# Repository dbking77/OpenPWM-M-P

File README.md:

OpenPWM-M-P
===========

A single channel motor driver for dc brushed motors utiliizing a attiny and a ZXBM5210 motor driver

At this time, this project is distributed under the TAPR Open Hardware License: http://www.tapr.org/ohl.html

These drivers use a resistor to control the max trip current. 

We assume that the desired trip current is right at the max for the driver, ow, 2 amps. 

Using the examples supplied in the data sheet, we would need a 0.25 ohm Rs resistor. Though, that resistor would need to be a 1 watt resistor. 

We would like to make the resistor smaller than a 1 watt surface mount resistor. So, we made the pad a 0805 pad. The max dissipation you can get out of a 0805 resistor is 1/3 watt. 

By altering VRef, we can alter the power disapated by the resistor. 

The resistor will see connect upto VRfef and ground.

If we select a lower cost resistor of 0.047 ohms ( http://www.digikey.com/scripts/DkSearch/dksus.dll?Detail&itemSeq=165686396 )

The equation for what the trip current(assuming that the trip current is 2) is:

ItripMax(2) = Vref / (Rs * 10)
2 = Vref / 0.47
Vref = 0.94V

The resistor should only see 0.04 watts if Vref is kept to 0.94.

Project owned by Michael Gregg(mgregg@-at-@michaelgregg.com) and Derr(dbking77@-at@gmail.com)

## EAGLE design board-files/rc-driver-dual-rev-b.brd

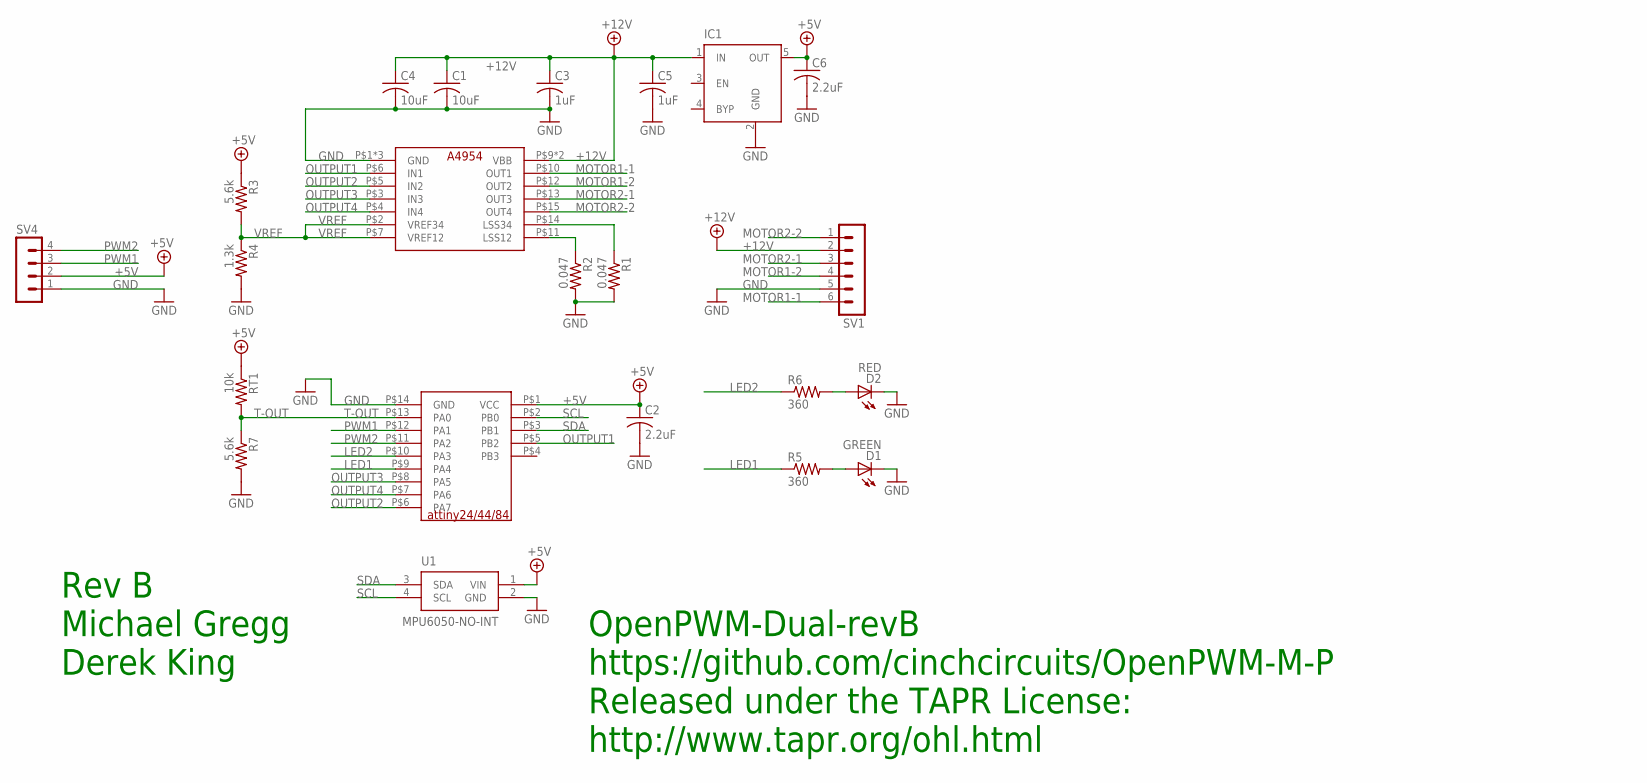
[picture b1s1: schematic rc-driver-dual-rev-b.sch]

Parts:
C1, C4: 10uF; C1206
C2, C6: 2.2uF; C0603
C3, C5: 1uF; C0603
D1: GREEN; CHIPLED_0603
D2: RED; CHIPLED_0603
IC1: MIC5219XX; SOT23-5; MPN TPS70950
R1, R2: 0.047; R0805
R3, R7: 5.6k; R0402
R4: 1.3k; R0402
R5, R6: 360; R0402
RT1: 10k; R0402
SV1: MA06-1
SV4: MA04-1
U1: MPU6050-NO-INT
U$1: ATTINY24A; SOIC-14-WIDE
U$2: A4954-DUAL-HBRIDGE; TSSOP-16-LP

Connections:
+5V: C2.1, C6.1, IC1.5 (OUT), R3.1, RT1.1, SV4.2, U1.1 (VIN), U$1.P$1 (VCC)
+12V: C1.1, C3.1, C4.1, C5.1, IC1.1 (IN), SV1.2, U$2.P$9 (VBB), U$2.P$16 (VBB)
GND: C1.2, C2.2, C3.2, C4.2, C5.2, C6.2, D1.C, D2.C, IC1.2 (GND), R1.2, R2.2, R4.2, R7.2, SV1.5, SV4.1, U1.2 (GND), U$1.P$14 (GND), U$2.P$1 (GND), U$2.P$8 (GND), U$2.P$17 (GND)
LED1: R5.1, U$1.P$9 (PA4)
LED2: R6.1, U$1.P$10 (PA3)
MOTOR1-1: SV1.6, U$2.P$10 (OUT1)
MOTOR1-2: SV1.4, U$2.P$12 (OUT2)
MOTOR2-1: SV1.3, U$2.P$13 (OUT3)
MOTOR2-2: SV1.1, U$2.P$15 (OUT4)
unnamed: R1.1, U$2.P$14 (LSS34)
unnamed: R2.1, U$2.P$11 (LSS12)
unnamed: D2.A, R6.2
unnamed: D1.A, R5.2
OUTPUT1: U$1.P$5 (PB2), U$2.P$6 (IN1)
OUTPUT2: U$1.P$6 (PA7), U$2.P$5 (IN2)
OUTPUT3: U$1.P$8 (PA5), U$2.P$3 (IN3)
OUTPUT4: U$1.P$7 (PA6), U$2.P$4 (IN4)
PWM1: SV4.3, U$1.P$12 (PA1)
PWM2: SV4.4, U$1.P$11 (PA2)
SCL: U1.4 (SCL), U$1.P$2 (PB0)
SDA: U1.3 (SDA), U$1.P$3 (PB1)
T-OUT: R7.1, RT1.2, U$1.P$13 (PA0)
VREF: R3.2, R4.1, U$2.P$2 (VREF34), U$2.P$7 (VREF12)

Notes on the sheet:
OpenPWM-Dual-revB
https://github.com/cinchcircuits/OpenPWM-M-P
Released under the TAPR License:
http://www.tapr.org/ohl.html
Rev B
Michael Gregg
Derek King

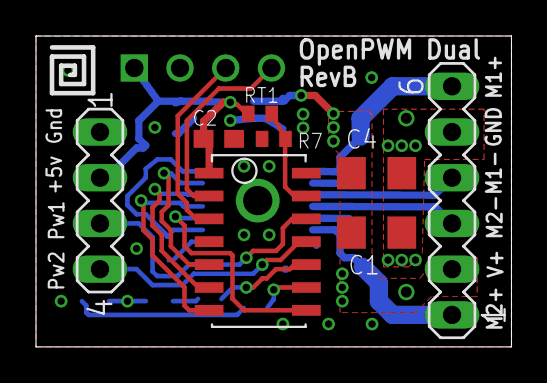
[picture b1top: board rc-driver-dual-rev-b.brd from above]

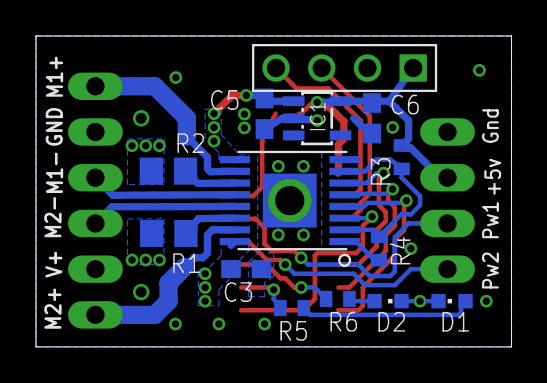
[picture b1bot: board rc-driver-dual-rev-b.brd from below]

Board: 2 copper layers, 26.4 x 17.3 mm, 22 parts (14 on the bottom side), 23 nets.

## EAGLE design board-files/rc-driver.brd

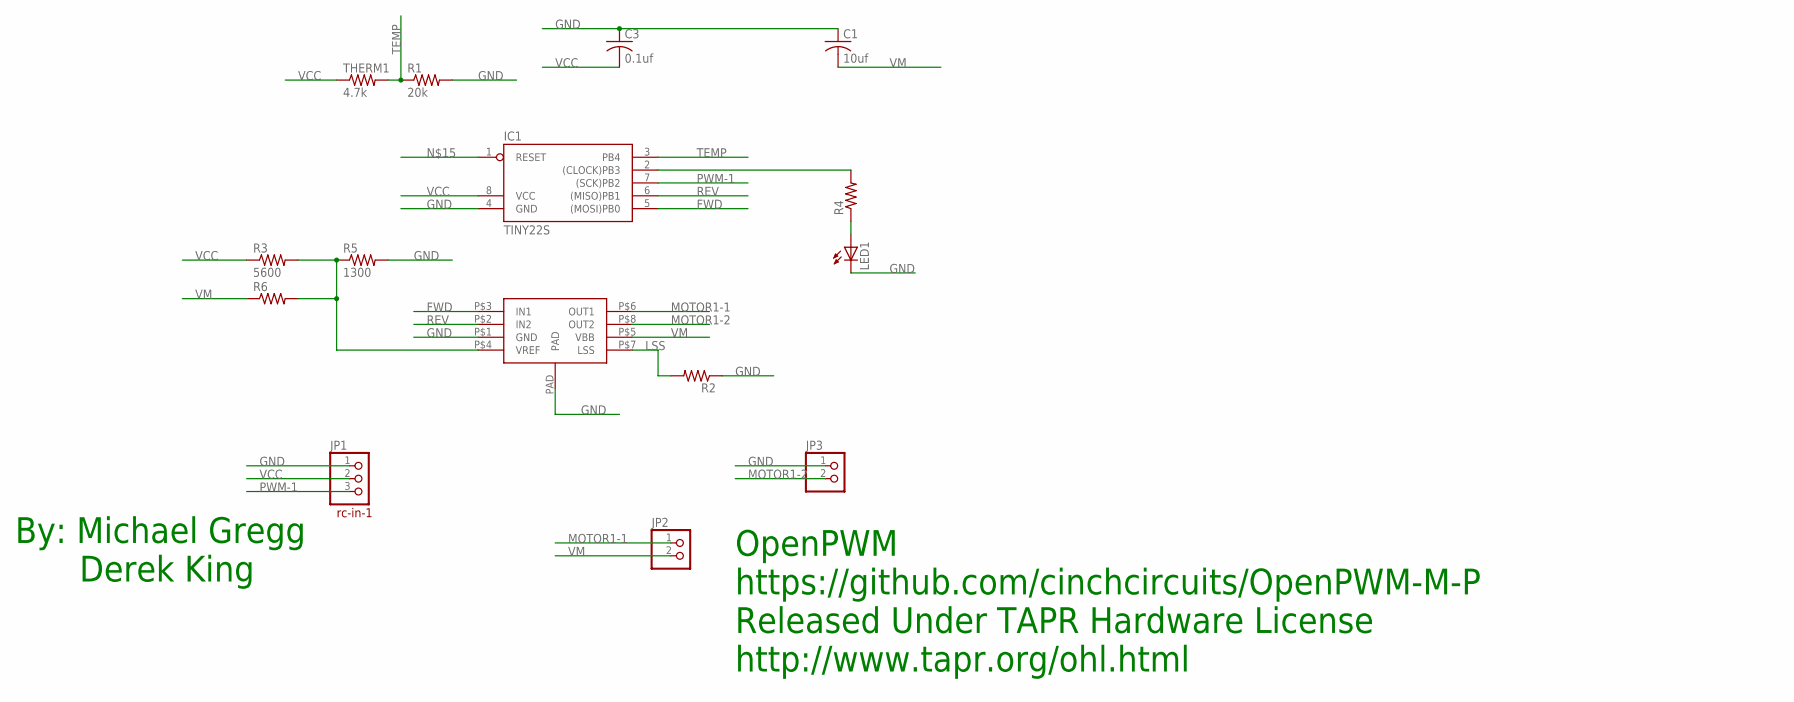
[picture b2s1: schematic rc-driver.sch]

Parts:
C1: 10uf; C1210
C3: 0.1uf; C0805
IC1: TINY22S; SOIC8
JP1: PINHD-1X3; 1X03
JP2, JP3: PINHD-1X2; 1X02
LED1: LEDCHIP-LED0603; CHIP-LED0603
R1: 20k; R0603
R2: R-US_R0805W; R0805W
R3: 5600; R0603
R4, R6: R-US_R0603; R0603
R5: 1300; R0603
THERM1: 4.7k; R0603
U$1: A4950-HBRIDGE; SO-8EP

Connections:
FWD: IC1.5 ((MOSI)PB0), U$1.P$3 (IN1)
GND: C1.1, C3.1, IC1.4 (GND), JP1.1, JP3.1, LED1.C, R1.2, R2.1, R5.2, U$1.P$1 (GND), U$1.PAD
LSS: R2.2, U$1.P$7 (LSS)
MOTOR1-1: JP2.1, U$1.P$6 (OUT1)
MOTOR1-2: JP3.2, U$1.P$8 (OUT2)
unnamed: R3.2, R5.1, R6.2, U$1.P$4 (VREF)
unnamed: IC1.2 ((CLOCK)PB3), R4.2
unnamed: LED1.A, R4.1
PWM-1: IC1.7 ((SCK)PB2), JP1.3
REV: IC1.6 ((MISO)PB1), U$1.P$2 (IN2)
TEMP: IC1.3 (PB4), R1.1, THERM1.2
VCC: C3.2, IC1.8 (VCC), JP1.2, R3.1, THERM1.1
VM: C1.2, JP2.2, R6.1, U$1.P$5 (VBB)

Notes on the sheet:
rc-in-1
By: Michael Gregg
Derek King
OpenPWM
https://github.com/cinchcircuits/OpenPWM-M-P
Released Under TAPR Hardware License
http://www.tapr.org/ohl.html

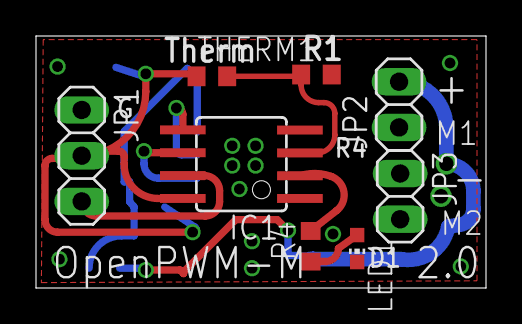
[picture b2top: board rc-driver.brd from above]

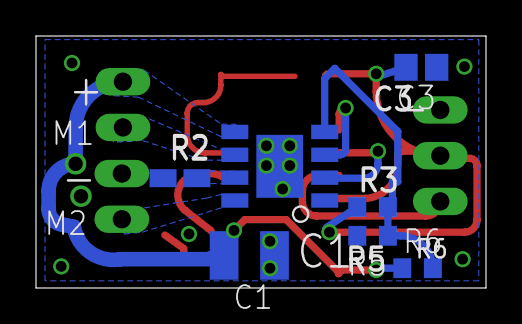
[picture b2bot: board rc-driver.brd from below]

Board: 2 copper layers, 25.0 x 14.0 mm, 15 parts (7 on the bottom side), 13 nets.

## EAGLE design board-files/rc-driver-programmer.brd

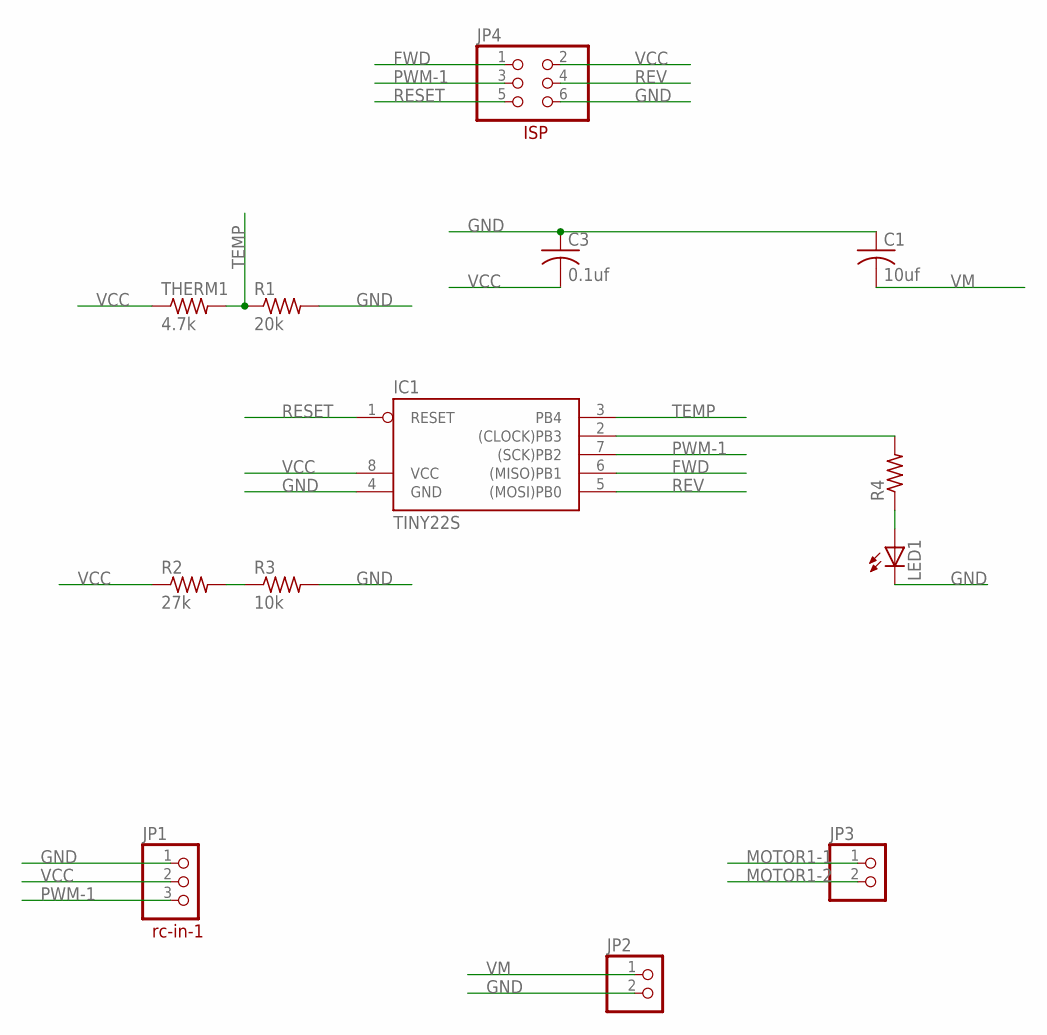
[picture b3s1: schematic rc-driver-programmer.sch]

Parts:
C1: 10uf; C1210
C3: 0.1uf; C0805
IC1: TINY22S; SOIC8
JP1: PINHD-1X3; 1X03
JP2, JP3: PINHD-1X2; 1X02
JP4: PINHD-2X3; 2X03
LED1: LEDCHIP-LED0603; CHIP-LED0603
R1: 20k; R0603
R2: 27k; R0603
R3: 10k; R0603
R4: R-US_R0603; R0603
THERM1: 4.7k; R0603

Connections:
FWD: IC1.6 ((MISO)PB1), JP4.1
GND: C1.1, C3.1, IC1.4 (GND), JP1.1, JP2.2, JP4.6, LED1.C, R1.2, R3.2
MOTOR1-1: JP3.1
MOTOR1-2: JP3.2
unnamed: IC1.2 ((CLOCK)PB3), R4.2
unnamed: LED1.A, R4.1
unnamed: R2.2, R3.1
PWM-1: IC1.7 ((SCK)PB2), JP1.3, JP4.3
RESET: IC1.1 (RESET), JP4.5
REV: IC1.5 ((MOSI)PB0), JP4.4
TEMP: IC1.3 (PB4), R1.1, THERM1.2
VCC: C3.2, IC1.8 (VCC), JP1.2, JP4.2, R2.1, THERM1.1
VM: C1.2, JP2.1

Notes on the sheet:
rc-in-1
ISP

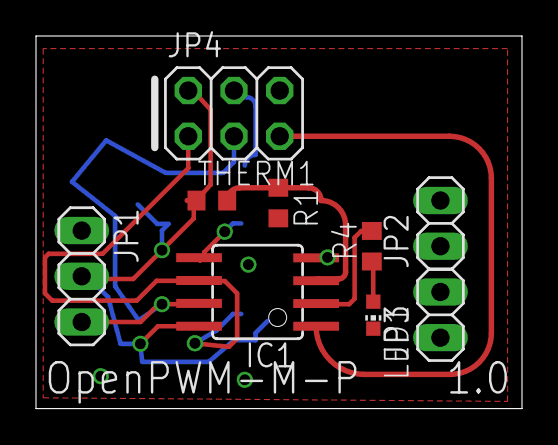
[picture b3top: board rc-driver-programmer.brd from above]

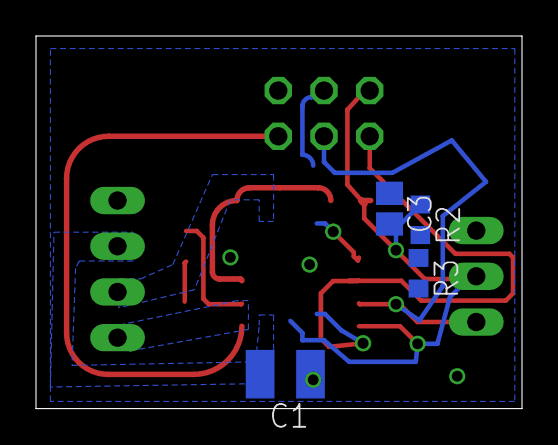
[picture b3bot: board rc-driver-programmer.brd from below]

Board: 2 copper layers, 27.0 x 20.7 mm, 13 parts (4 on the bottom side), 11 nets.

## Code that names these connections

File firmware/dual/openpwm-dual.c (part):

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#define PWM2_PIN 2

// Used to indicate error has occurred
#define LED2_PORT PORTA
#define LED2_DDR DDRA
#define LED2_PIN 3

// Used to indicate that input signal is being recv'ed
#define LED1_PORT PORTA
#define LED1_DDR DDRA
#define LED1_PIN 4


void gpioInit()
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    (0<<TOUT_PIN) |
    (0<<PWM1_PIN) |
    (0<<PWM2_PIN) |
    (1<<LED2_PIN) | 
    (1<<LED1_PIN) |
    (1<<OUT3_PIN) |
    (1<<OUT4_PIN) |
    (1<<OUT2_PIN) ;
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  PORTA =
    (1<<PWM1_PIN) |
    (1<<PWM2_PIN) |
    (1<<LED2_PIN) |
    (1<<LED1_PIN) ;
  
  DDRB = 
    (1<<OUT1_PIN);
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 *  output1 and output2 are a pair
 *  output2 and output4 are a pair
 *  
 *  output1 : PB2 : OC0A
 *  output2 : PA7 : OC0B
 *  output3 : PA5 : OC1B
 *  output4 : PA6 : OC1A
 */


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 *    value of -255 = full reverse
 *    value of 0 = stop/brake
 * 
 * out1 = PB2 = OC0A
 * out2 = PA7 = OC0B
 */
void setMotor1(int16_t duty)
{
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 *    value of -255 = full reverse
 *    value of 0 = stop/brake
 * 
 * out3 = PA5 = OC1B
 * out4 = PA6 = OC1A
 */
void setMotor2(int16_t duty)
{
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  {
    ++cnt.hi;
    // debug toggle LED everytime this occurs
    //LED2_PORT ^= (1<<LED2_PIN);
  }
  return cnt.val;
}
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    else
    {
      // debug toggle LED when bad pulse width is seen
      // LED1_PORT ^= (1<<LED1_PIN);
    }
  }
}
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 * generate a 16bit timestamp value that alows a servo pulse between
 * 1 and 2ms to be measured.
 * 
 * PA1 : PWM1 : PCINT1
 * PA2 : PWM2 : PCINT2
 */
uint8_t pcint_last_in;
ISR(PCINT0_vect)
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  // measure servo pwm pulse
  TIMSK0 = (1<<TOIE0);  

  // Enabled PCINT1 and PCINT2 for PA1 and PA2 pin change interrupts
  PCMSK0 = (1<<PCINT1) | (1<<PCINT2);
  GIMSK = (1<<PCIE0);
  pcint_last_in = PINA;
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      if (ovf_counter > 62)
      {
        ovf_counter = 0;
        //LED1_PORT ^= (1<<LED1_PIN);
        // when overflow counter reaches 62 it means about 
        // 62*256/8Mhz = 1.984ms have elapsed
        uint16_t time = getTimestamp();
        if (timeoutServoPwm(&pwm1, time) || timeoutServoPwm(&pwm2, time))
        {
          // servo signals stopped comming in, disable motors
          LED1_PORT &= ~(1<<LED1_PIN);
          LED2_PORT |= (1<<LED2_PIN);
          disableMotors();
          stable_counter = 0;
        }
        else 
        {
          LED1_PORT |= (1<<LED1_PIN);
          LED2_PORT &= ~(1<<LED2_PIN);

          // calculate new duty values from servo values
          // assume:
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
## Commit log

2014-12-25 Updating README.md to include license and ownership info.
2014-12-25 Adding first version of the board files. Including the gerbers used at seeedstudio
2014-12-28 Simple Makefile and some intialization code.
2015-01-04 Servo input capture and motor output is working. Settings for avrdude firmware and fuse programming Working servo input capture code with detection of lost signal. Hard-coded scaling from servo pulse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
2015-01-04 Rescale servo input based on mixed signal ranges. Put change limit and filter on servo signal to prevent over-current caused by changing stick too quickly.
2015-01-04 Reduce limits slightly for high voltage suply.
2015-01-04 Rescale servo input based on ranges of mixed signals from RC controller. Put filter and change limiter on PWM signal to prevent over-current caused by moving stick too quickly.
2015-01-13 Added start os v 2.0 files. Need to connect vref.
2015-01-18 Adding RC net to VREF. Creating gerbers for plain board.
2015-01-22 Adding start of dual motor driver and library.
2015-01-22 Removing uneeded library
2015-01-23 Added motor driver to dual driver board.
2015-01-26 fixing attiny silk. Shortened single rc-driver board.
2015-01-27 Added license to boards. Finished routingand silks.
2015-01-28 add drunken spriral
2015-01-30 Move squigly lines and extra capacitance on VM.
2015-01-30 Adding some final touches to the boards. Converting fonts to Vector.
2015-02-01 Updating readme.
2015-02-12 Moving single board files to different folder.
2015-02-14 Untested code for PWM on second motor output.
2015-02-15 Fixed edge-case bug in duty conversion.
2015-02-15 Update duty calculation of solo output device. Got servo pwm pulse capture working. Need to implment timeout.
2015-02-15 Detection of lost signal and overly long pulse widths.
2015-02-15 Fixed bug in TIM1 PWM setup. Added mixing and scaling of inputs to produce pwm. Added filter and deadzone to servo pwm.
2015-02-15 Reveres forward.
2015-04-03 Add brown-out detection. Have code wait for stable signal before starting motors.
2015-08-08 Changes for battlebot competition. More part information. Changed steering and forward direction mixing. Have one led for signal, and the other for no signal.
2015-08-09 Add hex file so compiler is not needed to program board.
2015-08-10 Copying dual board design to start rev B.
2015-08-10 First pass layout of revB designed that include 5V regulator Improved part outlines in library.
2015-08-24 Added optional 6-DOF IMU to circuit board. Changed some parts to 0402.
2015-11-23 Fix motor directionality for rev B MCBs.

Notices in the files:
firmware/dual/openpwm-dual.c:
Copyright (c) 2015, Derek King
All rights reserved.
